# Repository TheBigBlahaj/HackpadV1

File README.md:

# Elliott's HackPad!!
My first project through hackclub!!! I kinda feel like I missed out on a lot by learning about hackclub so late in highschool :(( but I'm coping by doing this (also hi Sam:3 ) I'm mostly doing this for learn a bit about python, kicad, and making pcbs. Probably just gonna use it for macros and such but I do wanna add some lights that react to keys being pushed because I think it's cool :3

## Features
- 4 Switches, each with an assigned macro
- 4 LEDs 
- Volume knob
- A monochrome .091" OLED display for animations

## CAD 
Made with a combo of Fusion and Onshape! (dont ask...)

You'll need to make a I2C wire to plug the OLED into the pin header on the PCB

## PCB

| **Schematic** | **PCB** |
|---------------|---------|
|||

Had to redo the routing like 5 times but it should all be good now X3

## Firmware 

Still a work in progress!!! Im using kmk to write it, but I have a lot to learn first tho....\
<sub>I've never used python before:3</sub>

## [BOM](https://raw.githubusercontent.com/TheBigBlahaj/HackpadV1/refs/heads/main/HackPad%20BOM.csv) <sub>linked the csv here</sub> 
- 1x Case (From CAD file)
- 1x Seeed XIAO RP2040 
- 1x 0.91 inch OLED 
- 1x EC11 Rotary Encoder
- 4x Cherry MX Switches
- 4x DSA Keycaps
- 4x SK6812 MINI-E LEDs
- 4x M3x16mm screws
- 4x M3x5mx4mm heatset inserts

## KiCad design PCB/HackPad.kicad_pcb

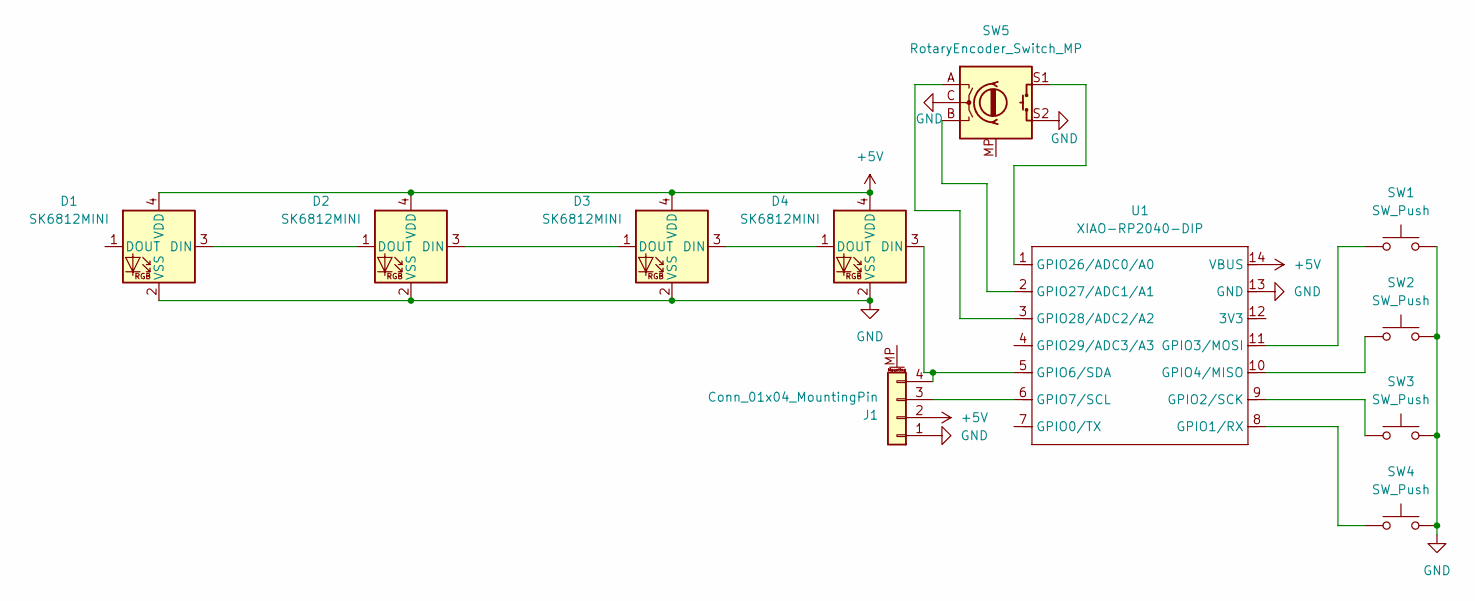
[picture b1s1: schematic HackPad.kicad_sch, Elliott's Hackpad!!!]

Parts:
D1, D2, D3, D4: SK6812MINI; LED_SK6812MINI_PLCC4_3.5x3.5mm_P1.75mm
J1: Conn_01x04_MountingPin; PinHeader_1x04_P2.54mm_Vertical
SW1, SW2, SW3, SW4: SW_Push; SW_Cherry_MX_1.00u_PCB
SW5: RotaryEncoder_Switch_MP; RotaryEncoder_Alps_EC11E-Switch_Vertical_H20mm
U1: XIAO-RP2040-DIP

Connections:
+5V: D1.4 (VDD), D2.4 (VDD), D3.4 (VDD), D4.4 (VDD), J1.2, U1.14 (VBUS)
GND: D1.2 (VSS), D2.2 (VSS), D3.2 (VSS), D4.2 (VSS), J1.1, SW1.1, SW2.1, SW3.1, SW4.1, SW5.C, SW5.S2, U1.13 (GND)
unnamed: D1.3 (DIN), D2.1 (DOUT)
unnamed: D2.3 (DIN), D3.1 (DOUT)
unnamed: D3.3 (DIN), D4.1 (DOUT)
unnamed: D4.3 (DIN), J1.4, U1.5 (GPIO6/SDA)
unnamed: J1.3, U1.6 (GPIO7/SCL)
unnamed: SW4.2, U1.8 (GPIO1/RX)
unnamed: SW3.2, U1.9 (GPIO2/SCK)
unnamed: SW1.2, U1.11 (GPIO3/MOSI)
unnamed: SW2.2, U1.10 (GPIO4/MISO)
unnamed: SW5.S1, U1.1 (GPIO26/ADC0/A0)
unnamed: SW5.B, U1.2 (GPIO27/ADC1/A1)
unnamed: SW5.A, U1.3 (GPIO28/ADC2/A2)

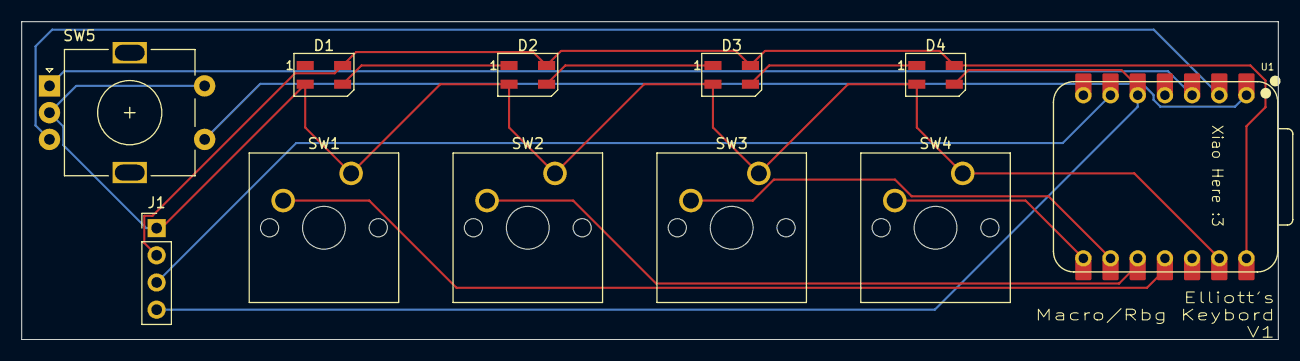
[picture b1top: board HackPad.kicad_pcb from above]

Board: 2 copper layers, 117.4 x 29.7 mm, 11 parts (0 on the bottom side), 14 nets.

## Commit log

2025-11-29 Setting up folders
2025-11-30 adding kicad /cad files
2025-11-30 added all me files and such, got some basic firmware cooked up
2025-12-02 added pictures to readme and fixed formatting
2025-12-02 fixing pictures
2025-12-02 again :(
2025-12-02 Done readme and ready for submit
2025-12-02 adding csv
2025-12-02 linked csv in readme
